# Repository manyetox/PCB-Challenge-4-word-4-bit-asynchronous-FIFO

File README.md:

# PCB Challenge 2026 – Submission

**Files**
- `pcb_challenge_final.kicad_pcb` / `.kicad_pro` / `.kicad_sch`: the KiCad 10 project. The schematic is unchanged from the challenge repo.
- `answer.md`: the logic deduction. The board is a 4-word × 4-bit asynchronous (dual-clock) FIFO.

## Board summary

| Item | Value |
|------|-------|
| Outline | Rectangle, **44 × 44 mm = 1936 mm²**. The Edge.Cuts line is 0.01 mm wide. |
| Content | 164 footprints, 411 vias (all 0.6/0.3 mm through vias) |
| Stack-up | 4 layers, 1.6 mm: F.Cu / 0.1 mm prepreg / In1.Cu / 1.24 mm core / In2.Cu / 0.1 mm prepreg / B.Cu |
| F.Cu | Components, signals, GND pour |
| In1.Cu | Solid GND plane. This is the reference for the USB D+/D− pair, which is routed on F.Cu with no vias, ≈28 mm long and length-matched. |
| In2.Cu | Signals plus a +3.3 V pour |
| B.Cu | Components, signals, GND pour |
| Rules (board setup + Default netclass) | 0.15 mm min track, 0.12 mm clearance, 0.6/0.3 mm vias (0.15 mm annular ring), 0.3 mm copper-to-edge, 0.25 mm hole-to-hole, 0.15 mm copper-to-hole |
| Power traces | +3.3 V / +5 V / GND are widened to 0.2–0.5 mm wherever clearance allows |
| Flip-flop pads (XSON6) | Only 0.15 mm tracks |

**Placement**
- Components are on both sides.
- The ESP32-S3 module sits in the top-right corner. Its antenna and antenna keep-out hang over the top board edge, which the rules allow.
- USB-C is on the bottom edge, below the module.

## Rule compliance

These were checked with KiCad's DRC and an independent script:
- **No unconnected items, no clearance, short or crossing errors.**
- **No vias inside any IC courtyard**, top or bottom. This includes the flip-flops' courtyard, which the library footprint places on the opposite side.
- **No foreign tracks inside an IC courtyard on the IC's own layer.** Each IC pin escapes straight out of its own pad.
- **The ESP32 module's ground pads** are a separate schematic net (`Net-(U25-GND-Pad2)`). They are joined by a small copper zone under the module, inside the pad ring.
- **Footprints are unmodified.**
  - SW2 and U25 were reloaded from the stock KiCad library, because the original PCB still had an old SW2 footprint.
  - Reference designators were moved to the Fab layers to keep the silkscreen clear. KiCad's library-mismatch check ignores this.

## Remaining DRC items (none come from the layout)
- `malformed_courtyard` on the XSON6 flip-flops (U1, U4…): this is the known flip-flop footprint issue mentioned in the challenge README.
- `lib_footprint_issues`: the custom `reg` / `adder` / `3v3_ldo` libraries are not installed on this machine.
- Schematic parity: symbol pins with no footprint pad. These are the NC pin 7 on the 6-pad muxes, J3's unused pins, and SW2 pins 3/4. They come from the provided schematic/footprints.
- Two `silk_edge_clearance` warnings. They are the ESP32's own silkscreen running past the board edge, where the antenna overhangs.

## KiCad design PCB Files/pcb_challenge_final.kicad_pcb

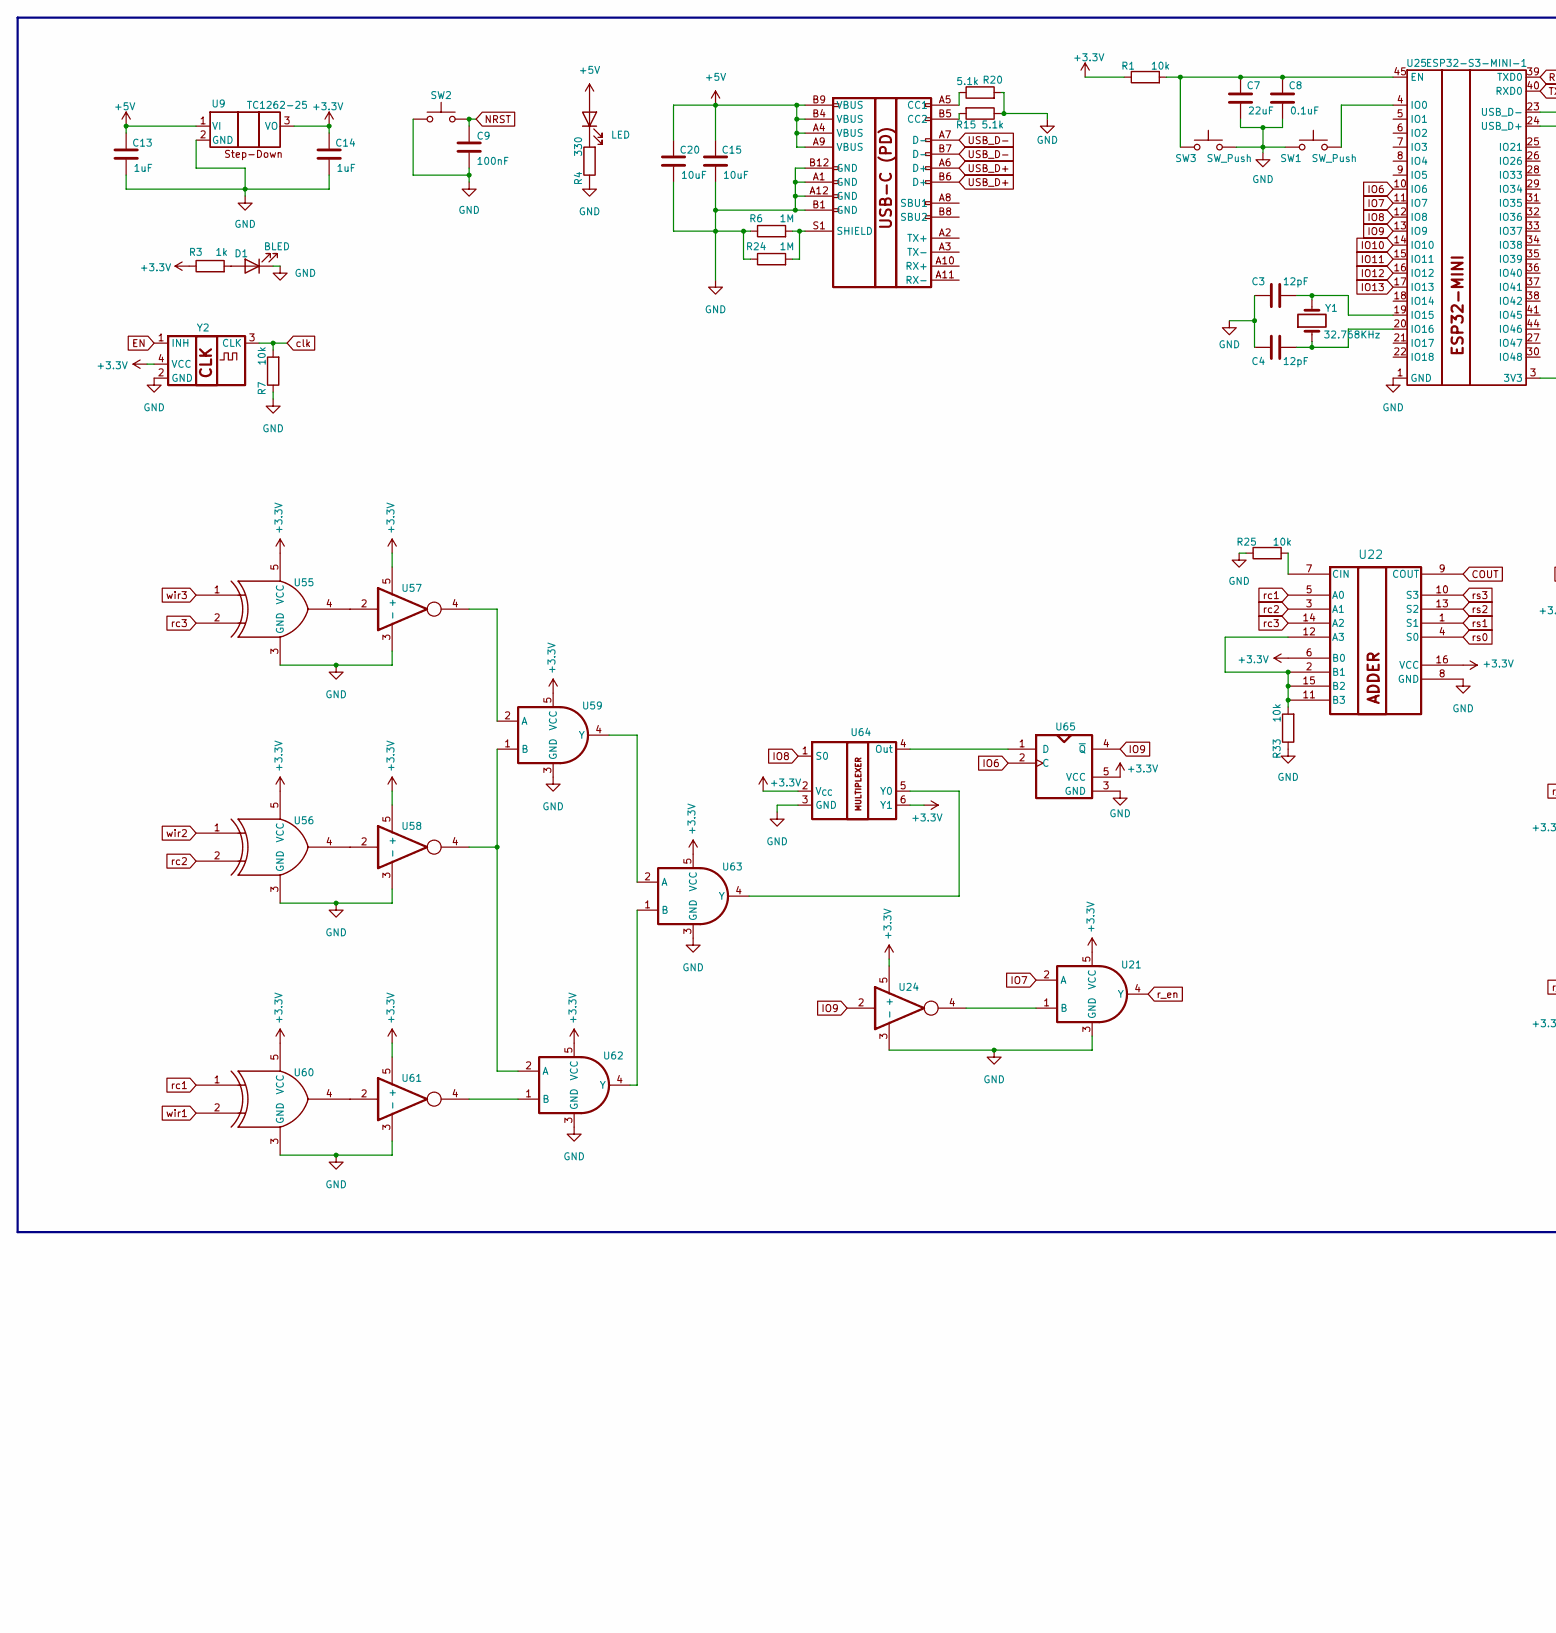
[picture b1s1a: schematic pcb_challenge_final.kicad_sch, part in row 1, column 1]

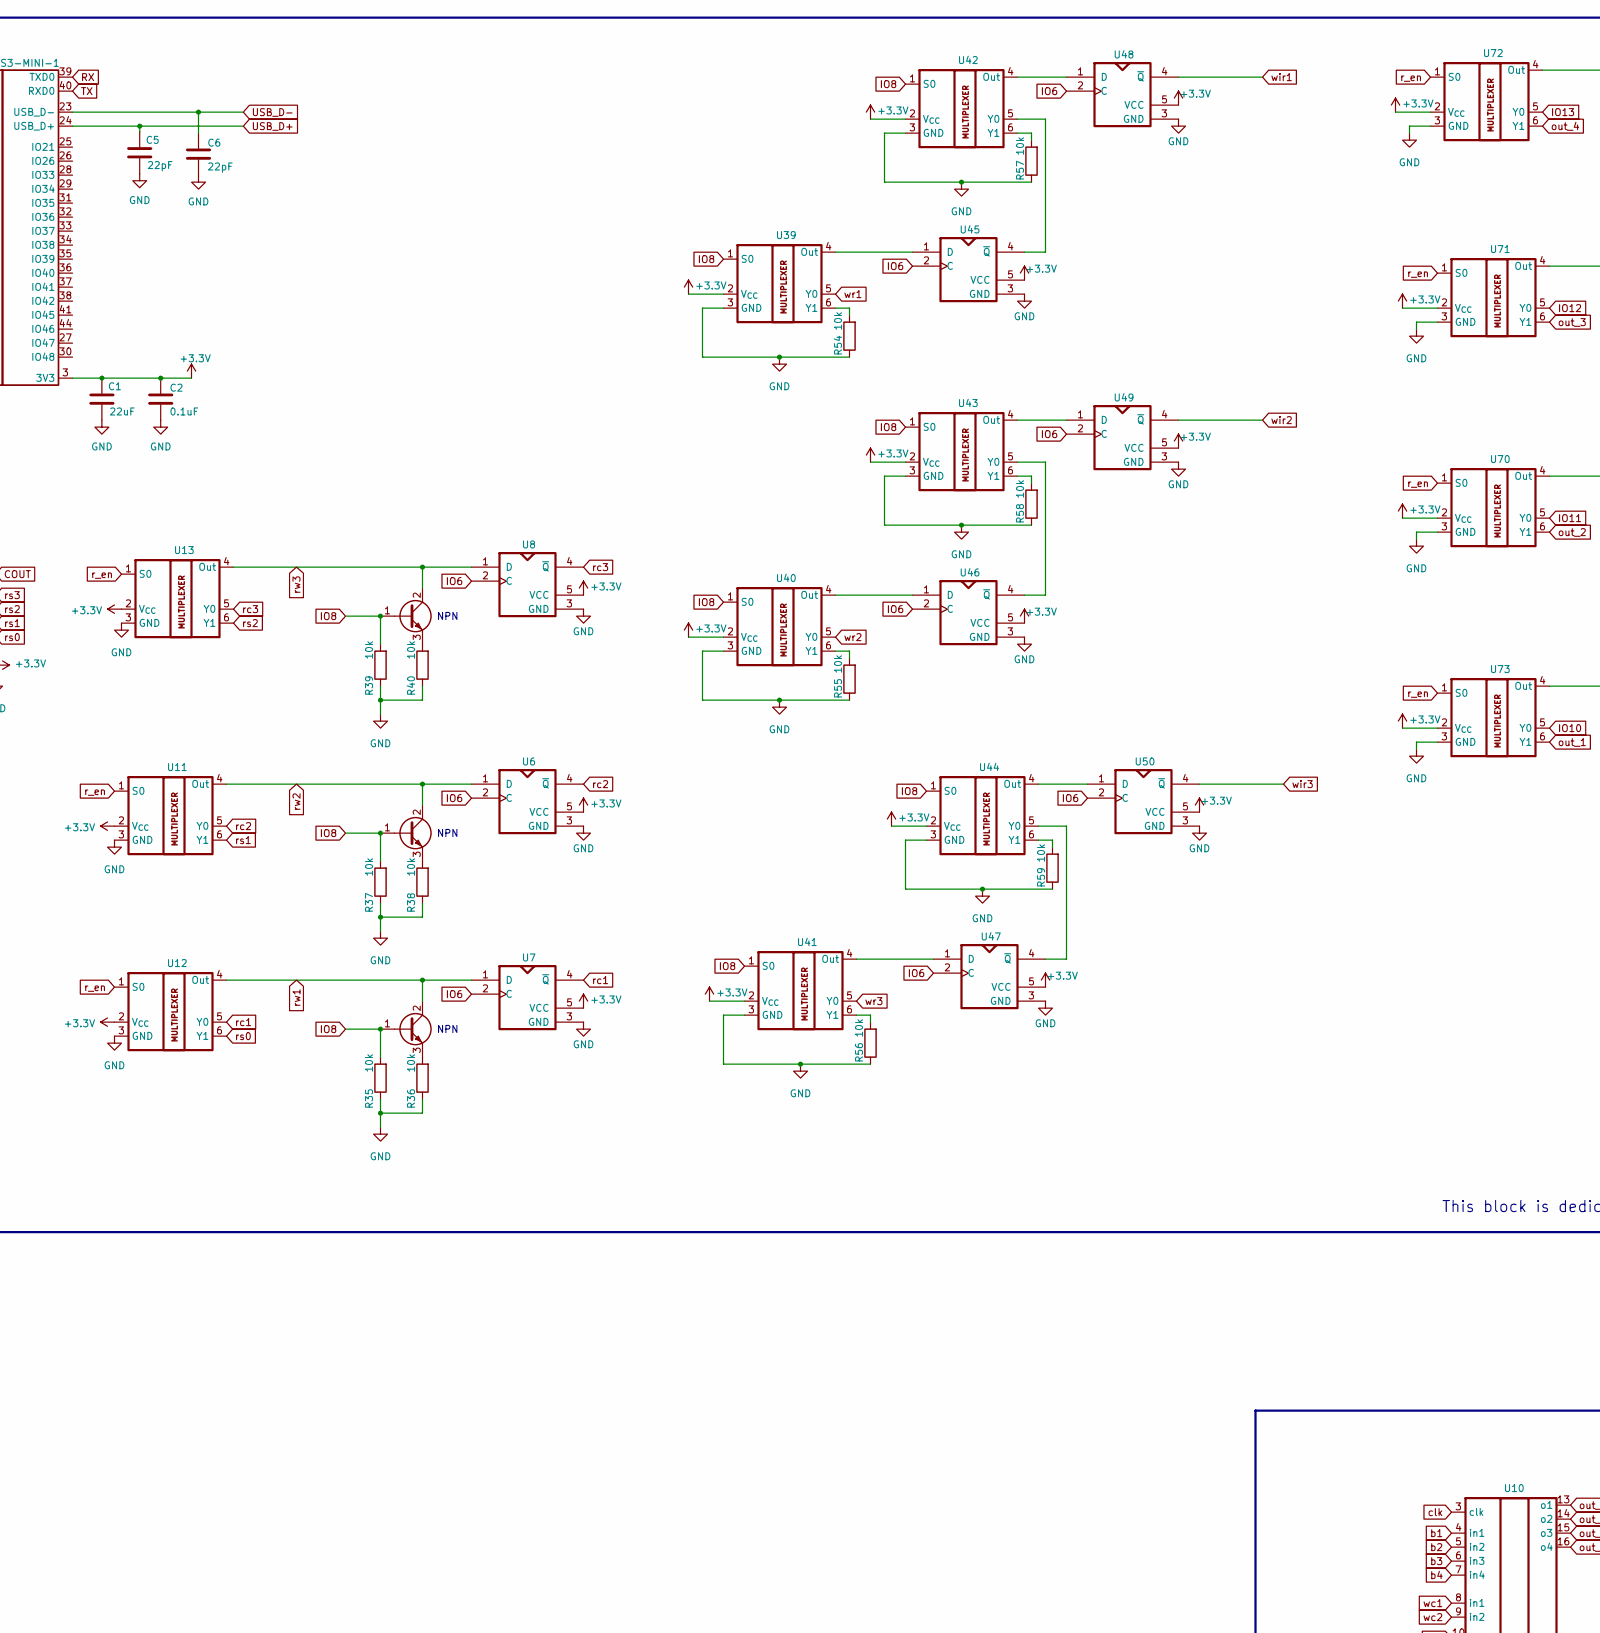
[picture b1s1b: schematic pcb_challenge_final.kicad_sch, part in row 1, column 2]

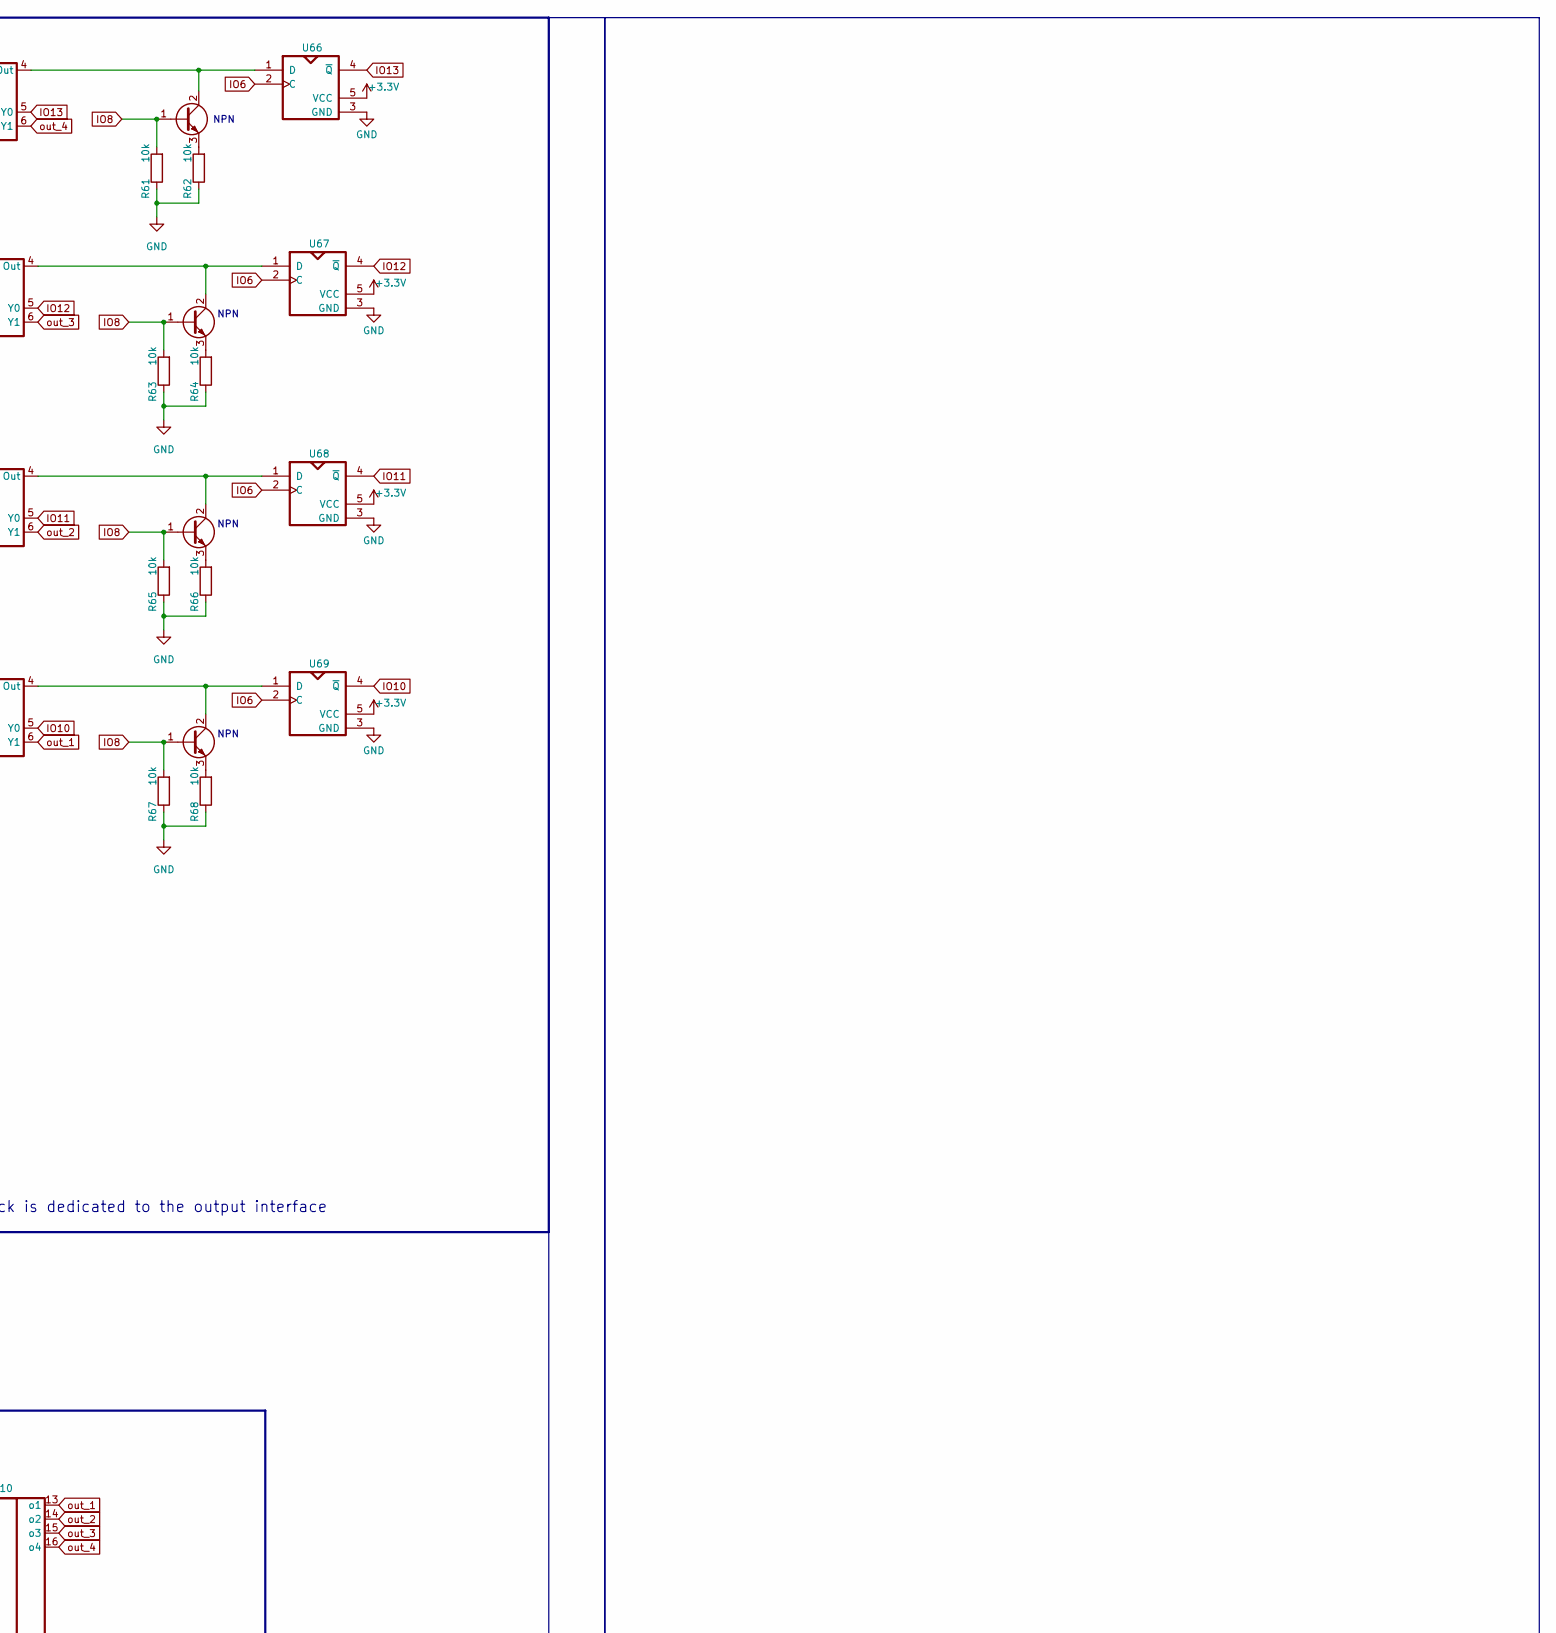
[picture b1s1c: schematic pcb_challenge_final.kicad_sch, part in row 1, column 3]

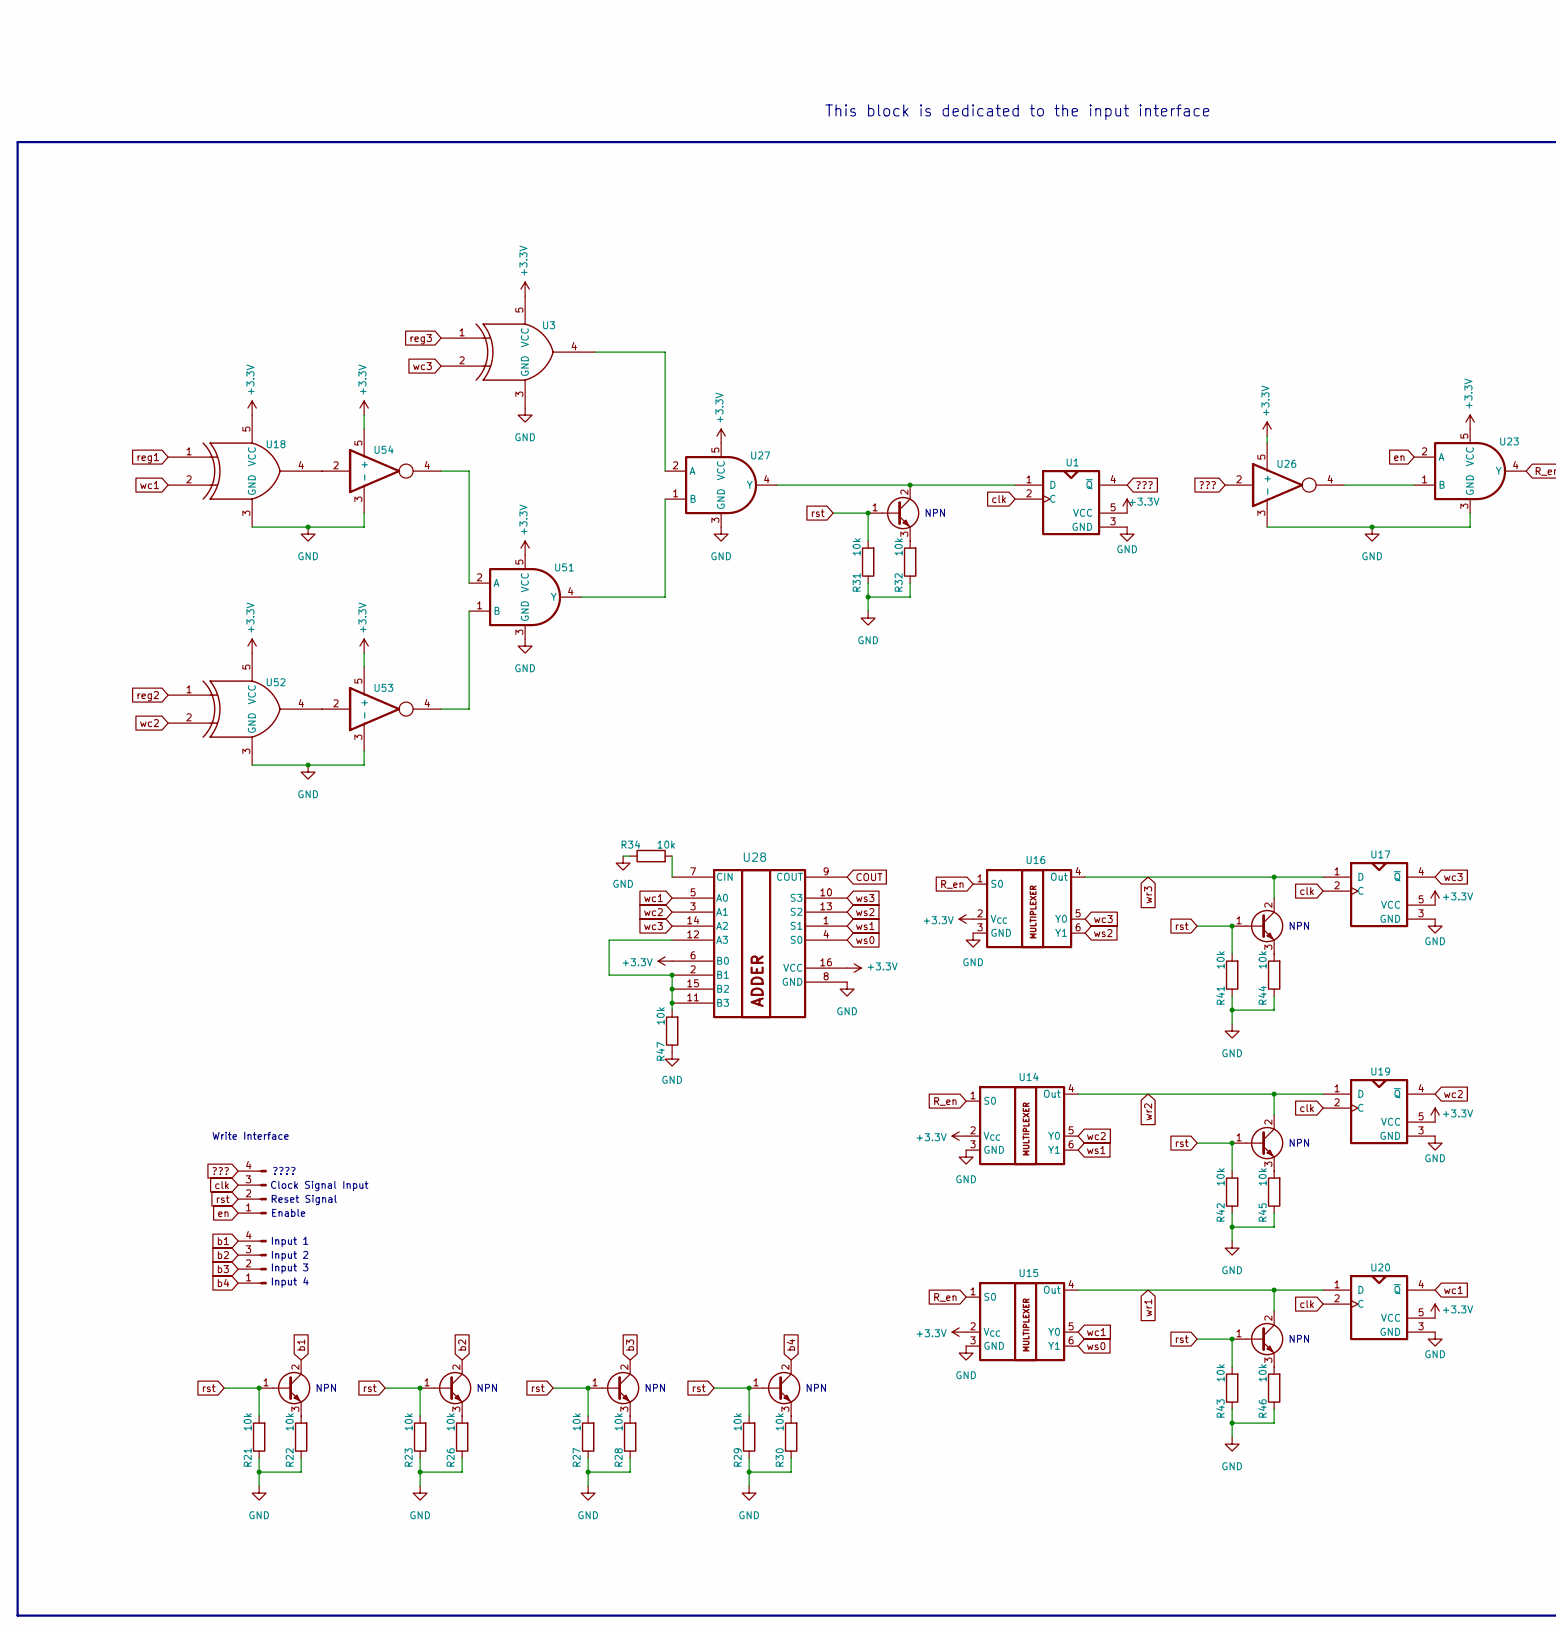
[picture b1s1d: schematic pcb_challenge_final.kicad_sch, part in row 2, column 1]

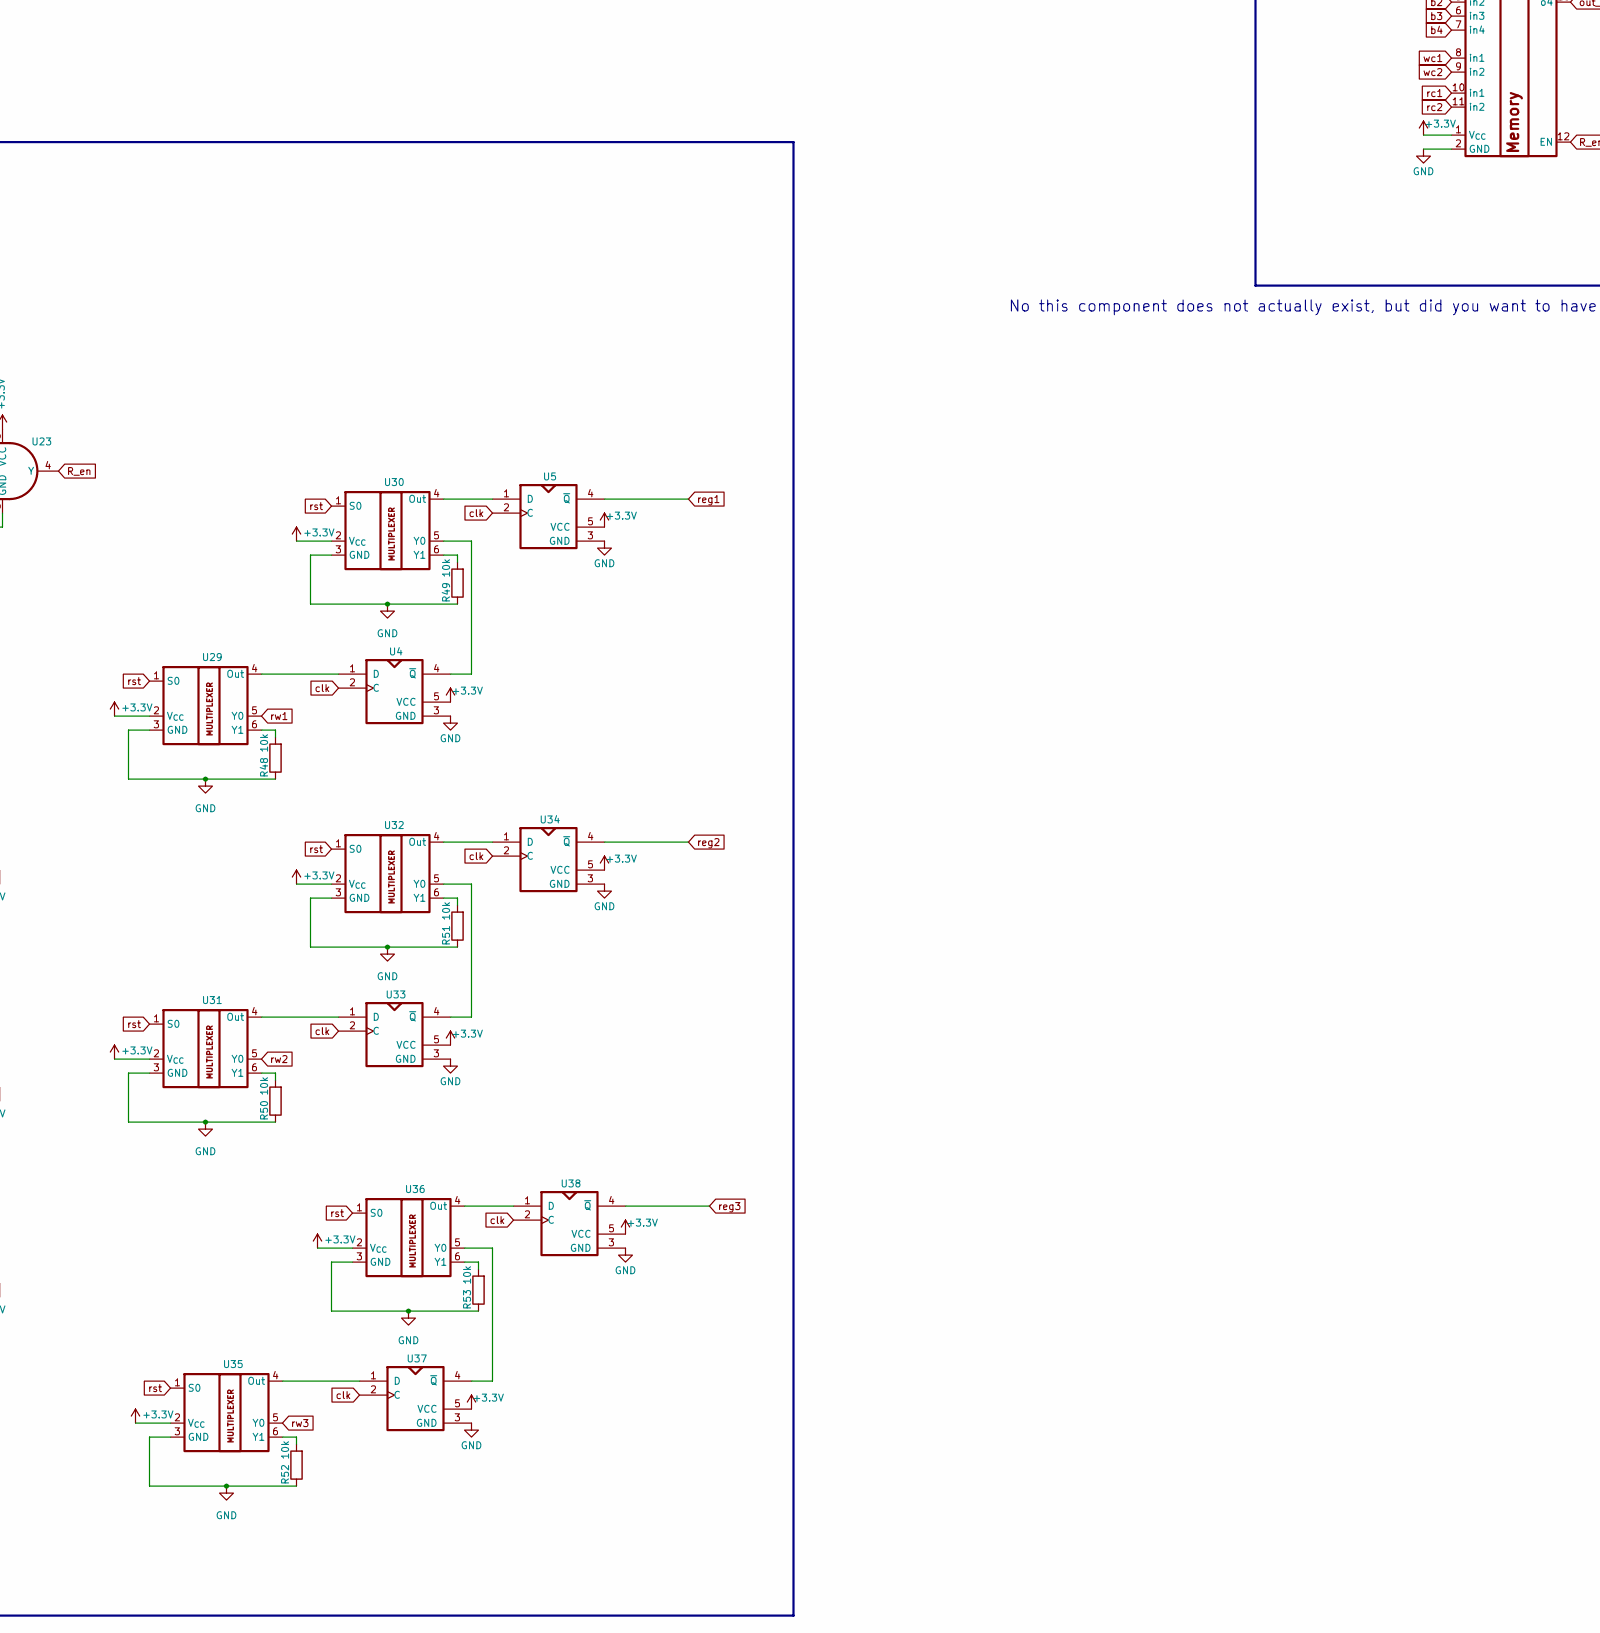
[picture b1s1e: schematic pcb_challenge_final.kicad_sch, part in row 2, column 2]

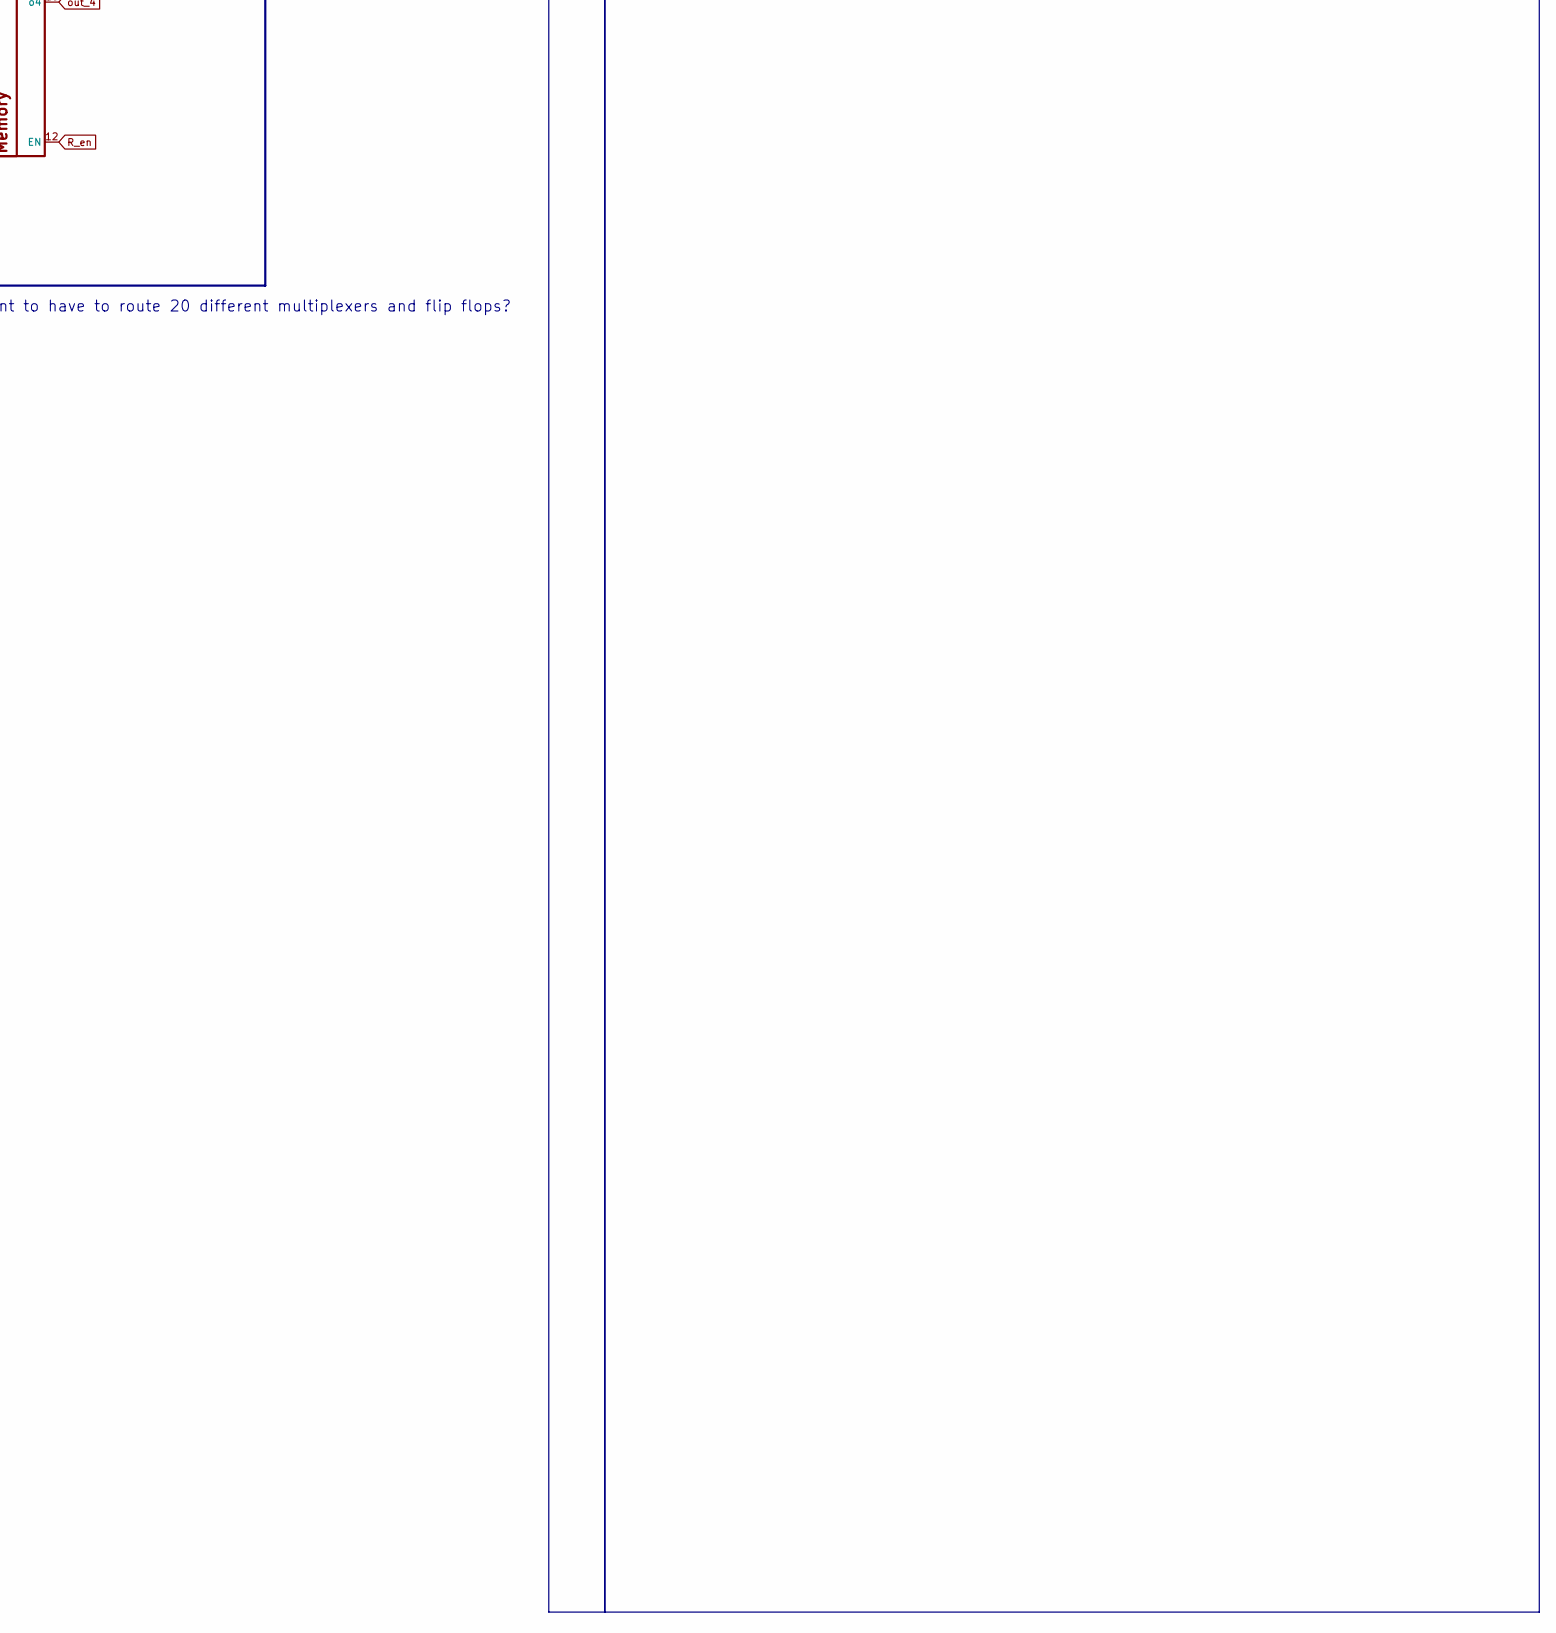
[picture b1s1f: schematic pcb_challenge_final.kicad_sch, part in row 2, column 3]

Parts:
C1, C7: 22uF; C_0201_0603Metric
C2, C8: 0.1uF; C_0201_0603Metric
C3, C4: 12pF; C_0201_0603Metric
C5, C6: 22pF; C_0201_0603Metric
C9: 100nF; C_0402_1005Metric
C13, C14: 1uF; C_0603_1608Metric
C15, C20: 10uF; C_0603_1608Metric
D1: BLED; LED_0603_1608Metric
GREEN_LED1: LED; LED_0603_1608Metric
J3: USB_C_Receptacle_HCTL_HC-TYPE-C-16P-01A
J4, J5: Conn_01x04_Pin; PinHeader_1x04_P2.54mm_Vertical
Q15, Q16, Q17, Q18, Q19, Q20, Q21, Q22, Q23, Q24, Q25, Q26, Q27, Q28, Q29: Q_Dual_NPN_PNP_B1E2B2C2E1C1; SOT-1123
R1: 10k; C_0402_1005Metric
R3: 1k; C_0603_1608Metric
R4: 330; C_0603_1608Metric
R6, R24: 1M; C_0603_1608Metric
R7, R21, R22, R23, R25, R26, R27, R28, R29, R30, R31, R32, R33, R34, R35, R36, R37, R38, R39, R40, R41, R42, R43, R44, R45, R46, R47, R48, R49, R50, R51, R52, R53, R54, R55, R56, R57, R58, R59, R61, R62, R63, R64, R65, R66, R67, R68: 10k; C_0603_1608Metric
R15, R20: 5.1k; R_0603_1608Metric_Pad0.98x0.95mm_HandSolder
SW1, SW3: SW_Push; SW_DIP_SPSTx01_Slide_6.7x4.1mm_W8.61mm_P2.54mm_LowProfile
SW2: SW_MEC_5G; SW_SPST_CK_RS282G05A3
U1, U4, U5, U6, U7, U8, U17, U19, U20, U33, U34, U37, U38, U45, U46, U47, U48, U49, U50, U65, U66, U67, U68, U69: 74AUP1G80; XSON6_SOT1115_NEX
U3, U18, U52, U55, U56, U60: 74AHC1G86; SC-74A-5_1.55x2.9mm_P0.95mm
U9: TC1262-25; SOT-223_3MC_MCH
U10: NMUX1308BQ; SO-16_3.9x9.9mm_P1.27mm
U11, U12, U13, U14, U15, U16, U29, U30, U31, U32, U35, U36, U39, U40, U41, U42, U43, U44, U64, U70, U71, U72, U73: NMUX1308BQ; SOT-363_SC-70-6
U21, U23, U27, U51, U59, U62, U63: 74LV1T08GV; SC-74A-5_1.55x2.9mm_P0.95mm
U22, U28: CD74HC283M96; D16
U24, U26, U53, U54, U57, U58, U61: 74LVC1GU04DRL; SOT-553
U25: ESP32-S3-MINI-1; ESP32-S2-MINI-1
Y1: 32.768KHz; Crystal_SMD_Abracon_ABM7-2Pin_6.0x3.5mm
Y2: KC2520Z; Oscillator_SMD_Kyocera_KC2520Z-4Pin_2.5x2.0mm

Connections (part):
+3.3V: C1.1, C2.1, C14.1, R1.1, R3.1, U1.5 (VCC), U3.5 (VCC), U4.5 (VCC), U5.5 (VCC), U6.5 (VCC), U7.5 (VCC), U8.5 (VCC), U9.3 (VO), U10.1 (V_{CC}), U11.2 (V_{CC}), U12.2 (V_{CC}), U13.2 (V_{CC}), U14.2 (V_{CC}), U15.2 (V_{CC}), U16.2 (V_{CC}), U17.5 (VCC), U18.5 (VCC), U19.5 (VCC), U20.5 (VCC), U21.5 (VCC), U22.6 (B0), U22.16 (VCC), U23.5 (VCC), U24.5 (+), U25.3 (3V3), U26.5 (+), U27.5 (VCC), U28.6 (B0), U28.16 (VCC), U29.2 (V_{CC}), U30.2 (V_{CC}), U31.2 (V_{CC}), U32.2 (V_{CC}), U33.5 (VCC), U34.5 (VCC), U35.2 (V_{CC}), U36.2 (V_{CC}), U37.5 (VCC), U38.5 (VCC), U39.2 (V_{CC}), U40.2 (V_{CC}), U41.2 (V_{CC}), U42.2 (V_{CC}), U43.2 (V_{CC}), U44.2 (V_{CC}), U45.5 (VCC), U46.5 (VCC), U47.5 (VCC), U48.5 (VCC), U49.5 (VCC), U50.5 (VCC), U51.5 (VCC), U52.5 (VCC), U53.5 (+), U54.5 (+), U55.5 (VCC), U56.5 (VCC), U57.5 (+), U58.5 (+), U59.5 (VCC), U60.5 (VCC), U61.5 (+), U62.5 (VCC), U63.5 (VCC), U64.2 (V_{CC}), U64.6 (Y1), U65.5 (VCC), U66.5 (VCC), U67.5 (VCC), U68.5 (VCC), U69.5 (VCC), U70.2 (V_{CC}), U71.2 (V_{CC}), U72.2 (V_{CC}), U73.2 (V_{CC})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
+5V: C13.1, C15.1, C20.1, GREEN_LED1.2 (A), J3.A4 (VBUS), J3.A9 (VBUS), J3.B4 (VBUS), J3.B9 (VBUS), U9.1 (VI)
???: J5.4, U1.4 (~Q), U26.2
COUT: U22.9 (COUT), U28.9 (COUT)
EN: Y2.1 (INH)
GND: C1.2, C2.2, C3.1, C4.1, C5.2, C6.2, C7.2, C8.2, C9.2, C13.2, C14.2, C15.2, C20.2, D1.1 (K), J3.A1 (GND), J3.A12 (GND), J3.B1 (GND), J3.B12 (GND), R4.1, R6.1, R7.1, R15.1, R20.2, R21.1, R22.1, R23.1, R24.1, R25.1, R26.1, R27.1, R28.1, R29.1, R30.1, R31.1, R32.1, R33.1, R34.1, R35.1, R36.1, R37.1, R38.1, R39.1, R40.1, R41.1, R42.1, R43.1, R44.1, R45.1, R46.1, R47.1, R48.1, R49.1, R50.1, R51.1, R52.1, R53.1, R54.1, R55.1, R56.1, R57.1, R58.1, R59.1, R61.1, R62.1, R63.1, R64.1, R65.1, R66.1, R67.1, R68.1, SW1.1, SW2.1 (A), SW2.2 (A), SW3.2, U1.3 (GND), U3.3 (GND), U4.3 (GND), U5.3 (GND), U6.3 (GND), U7.3 (GND)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
IO6: U6.2 (C), U7.2 (C), U8.2 (C), U25.10 (IO6), U45.2 (C), U46.2 (C), U47.2 (C), U48.2 (C), U49.2 (C), U50.2 (C), U65.2 (C), U66.2 (C), U67.2 (C), U68.2 (C), U69.2 (C)
IO7: U21.2 (A), U25.11 (IO7)
IO8: Q18.1 (B1), Q19.1 (B1), Q20.1 (B1), Q24.1 (B1), Q25.1 (B1), Q26.1 (B1), Q27.1 (B1), R35.2, R37.2, R39.2, R61.2, R63.2, R65.2, R67.2, U25.12 (IO8), U39.1 (S0), U40.1 (S0), U41.1 (S0), U42.1 (S0), U43.1 (S0), U44.1 (S0), U64.1 (S0)
IO9: U24.2, U25.13 (IO9), U65.4 (~Q)
IO10: U25.14 (IO10), U69.4 (~Q), U73.5 (Y0)
IO11: U25.15 (IO11), U68.4 (~Q), U70.5 (Y0)
IO12: U25.16 (IO12), U67.4 (~Q), U71.5 (Y0)
IO13: U25.17 (IO13), U66.4 (~Q), U72.5 (Y0)
NRST: C9.1, SW2.3 (B), SW2.4 (B)
unnamed: D1.2 (A), R3.2
unnamed: GREEN_LED1.1 (K), R4.2
unnamed: J3.A5 (CC1), R20.1
unnamed: J3.B5 (CC2), R15.2
unnamed: J3.S1 (SHIELD), R6.2, R24.2
unnamed: Q15.3 (E1), R30.2
unnamed: Q16.2 (C1), U1.1 (D), U27.4 (Y)
unnamed: Q16.3 (E1), R32.2
unnamed: Q17.3 (E1), R28.2
unnamed: Q18.3 (E1), R40.2
unnamed: Q19.3 (E1), R38.2
unnamed: Q20.3 (E1), R36.2
unnamed: Q21.3 (E1), R44.2
unnamed: Q22.3 (E1), R45.2
unnamed: Q23.3 (E1), R46.2
unnamed: Q24.2 (C1), U66.1 (D), U72.4 (Out)
unnamed: Q24.3 (E1), R62.2
unnamed: Q25.2 (C1), U67.1 (D), U71.4 (Out)
unnamed: Q25.3 (E1), R64.2
unnamed: Q26.2 (C1), U68.1 (D), U70.4 (Out)
unnamed: Q26.3 (E1), R66.2
unnamed: Q27.2 (C1), U69.1 (D), U73.4 (Out)
unnamed: Q27.3 (E1), R68.2
unnamed: Q28.3 (E1), R26.2
unnamed: Q29.3 (E1), R22.2
unnamed: U18.4, U54.2
unnamed: U21.1 (B), U24.4
unnamed: R33.2, U22.2 (B1), U22.11 (B3), U22.12 (A3), U22.15 (B2)
unnamed: R25.2, U22.7 (CIN)
unnamed: U23.1 (B), U26.4
unnamed: C7.1, C8.1, R1.2, SW3.1, U25.45 (EN)
unnamed: U25.2 (GND), U25.42 (GND), U25.43 (GND), U25.46 (GND), U25.47 (GND), U25.48 (GND), U25.49 (GND), U25.50 (GND), U25.51 (GND), U25.52 (GND), U25.53 (GND), U25.54 (GND), U25.55 (GND), U25.56 (GND), U25.57 (GND), U25.58 (GND), U25.59 (GND), U25.60 (GND), U25.61 (GND), U25.62 (GND), U25.63 (GND), U25.64 (GND), U25.65 (GND)
unnamed: SW1.2, U25.4 (IO0)
unnamed: C3.2, U25.19 (IO15), Y1.2
unnamed: C4.2, U25.20 (IO16), Y1.1
unnamed: U3.4, U27.2 (A)
unnamed: U27.1 (B), U51.4 (Y)
unnamed: R47.2, U28.2 (B1), U28.11 (B3), U28.12 (A3), U28.15 (B2)
unnamed: R34.2, U28.7 (CIN)
unnamed: U4.1 (D), U29.4 (Out)
unnamed: R48.2, U29.6 (Y1)
unnamed: U5.1 (D), U30.4 (Out)
unnamed: U4.4 (~Q), U30.5 (Y0)
unnamed: R49.2, U30.6 (Y1)
unnamed: U31.4 (Out), U33.1 (D)
unnamed: R50.2, U31.6 (Y1)
unnamed: U32.4 (Out), U34.1 (D)
unnamed: U32.5 (Y0), U33.4 (~Q)
unnamed: R51.2, U32.6 (Y1)
unnamed: U35.4 (Out), U37.1 (D)
unnamed: R52.2, U35.6 (Y1)
unnamed: U36.4 (Out), U38.1 (D)
unnamed: U36.5 (Y0), U37.4 (~Q)
unnamed: R53.2, U36.6 (Y1)
unnamed: U39.4 (Out), U45.1 (D)
unnamed: R54.2, U39.6 (Y1)
unnamed: U40.4 (Out), U46.1 (D)
unnamed: R55.2, U40.6 (Y1)
unnamed: U41.4 (Out), U47.1 (D)
unnamed: R56.2, U41.6 (Y1)
unnamed: U42.4 (Out), U48.1 (D)
unnamed: U42.5 (Y0), U45.4 (~Q)
unnamed: R57.2, U42.6 (Y1)
unnamed: U43.4 (Out), U49.1 (D)
unnamed: U43.5 (Y0), U46.4 (~Q)
unnamed: R58.2, U43.6 (Y1)
unnamed: U44.4 (Out), U50.1 (D)
unnamed: U44.5 (Y0), U47.4 (~Q)
unnamed: R59.2, U44.6 (Y1)
unnamed: U51.2 (A), U54.4
unnamed: U51.1 (B), U53.4
unnamed: U52.4, U53.2
unnamed: U55.4, U57.2
unnamed: U56.4, U58.2
unnamed: U57.4, U59.2 (A)
unnamed: U58.4, U59.1 (B), U62.2 (A)
unnamed: U59.4 (Y), U63.2 (A)
unnamed: U60.4, U61.2
unnamed: U61.4, U62.1 (B)
unnamed: U62.4 (Y), U63.1 (B)
unnamed: U63.4 (Y), U64.5 (Y0)
unnamed: U64.4 (Out), U65.1 (D)
RX: U25.39 (TXD0)
R_en: U10.12 (EN), U14.1 (S0), U15.1 (S0), U16.1 (S0), U23.4 (Y)
TX: U25.40 (RXD0)
USB_D+: C5.1, J3.A6 (D+), J3.B6 (D+), U25.24 (USB_D+)
USB_D-: C6.1, J3.A7 (D-), J3.B7 (D-), U25.23 (USB_D-)
b1: J4.4, Q29.2 (C1), U10.4 (in1)
b2: J4.3, Q28.2 (C1), U10.5 (in2)
b3: J4.2, Q17.2 (C1), U10.6 (in3)
b4: J4.1, Q15.2 (C1), U10.7 (in4)
clk: J5.3, R7.2, U1.2 (C), U4.2 (C), U5.2 (C), U10.3 (clk), U17.2 (C), U19.2 (C), U20.2 (C), U33.2 (C), U34.2 (C), U37.2 (C), U38.2 (C), Y2.3 (CLK)
en: J5.1, U23.2 (A)
out_1: U10.13 (o1), U73.6 (Y1)
out_2: U10.14 (o2), U70.6 (Y1)
out_3: U10.15 (o3), U71.6 (Y1)
out_4: U10.16 (o4), U72.6 (Y1)
r_en: U11.1 (S0), U12.1 (S0), U13.1 (S0), U21.4 (Y), U70.1 (S0), U71.1 (S0), U72.1 (S0), U73.1 (S0)
rc1: U7.4 (~Q), U10.10 (in1), U12.5 (Y0), U22.5 (A0), U60.1
rc2: U6.4 (~Q), U10.11 (in2), U11.5 (Y0), U22.3 (A1), U56.2
rc3: U8.4 (~Q), U13.5 (Y0), U22.14 (A2), U55.2
reg1: U5.4 (~Q), U18.1
reg2: U34.4 (~Q), U52.1
reg3: U3.1, U38.4 (~Q)
rs0: U12.6 (Y1), U22.4 (S0)
rs1: U11.6 (Y1), U22.1 (S1)
rs2: U13.6 (Y1), U22.13 (S2)
rs3: U22.10 (S3)
rst: J5.2, Q15.1 (B1), Q16.1 (B1), Q17.1 (B1), Q21.1 (B1), Q22.1 (B1), Q23.1 (B1), Q28.1 (B1), Q29.1 (B1), R21.2, R23.2, R27.2, R29.2, R31.2, R41.2, R42.2, R43.2, U29.1 (S0), U30.1 (S0), U31.1 (S0), U32.1 (S0), U35.1 (S0), U36.1 (S0)
rw1: Q20.2 (C1), U7.1 (D), U12.4 (Out), U29.5 (Y0)
rw2: Q19.2 (C1), U6.1 (D), U11.4 (Out), U31.5 (Y0)
rw3: Q18.2 (C1), U8.1 (D), U13.4 (Out), U35.5 (Y0)
wc1: U10.8 (in1), U15.5 (Y0), U18.2, U20.4 (~Q), U28.5 (A0)
wc2: U10.9 (in2), U14.5 (Y0), U19.4 (~Q), U28.3 (A1), U52.2
wc3: U3.2, U16.5 (Y0), U17.4 (~Q), U28.14 (A2)
wir1: U48.4 (~Q), U60.2
wir2: U49.4 (~Q), U56.1
wir3: U50.4 (~Q), U55.1
wr1: Q23.2 (C1), U15.4 (Out), U20.1 (D), U39.5 (Y0)
wr2: Q22.2 (C1), U14.4 (Out), U19.1 (D), U40.5 (Y0)
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
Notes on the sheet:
NPN
Reset Signal
This block is dedicated to the input interface
Clock Signal Input
Enable
Input 2
Input 3
No this component does not actually exist, but did you want to have to route 20 different multiplexers and flip flops?
????
Input 1
Input 4
Write Interface
This block is dedicated to the output interface

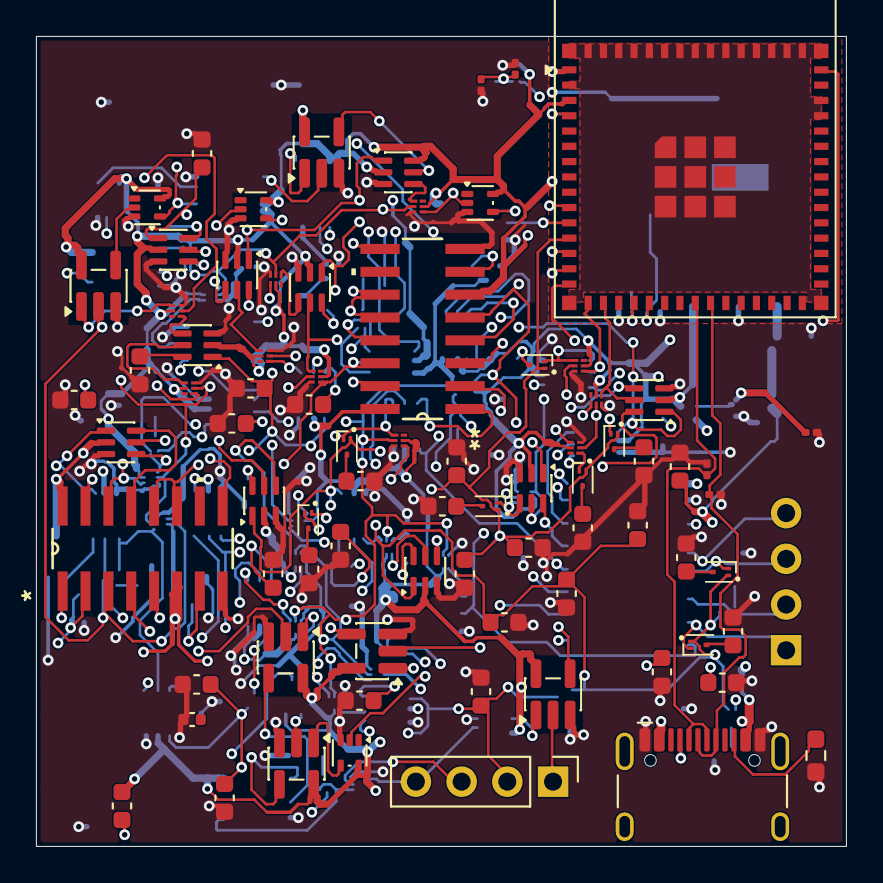
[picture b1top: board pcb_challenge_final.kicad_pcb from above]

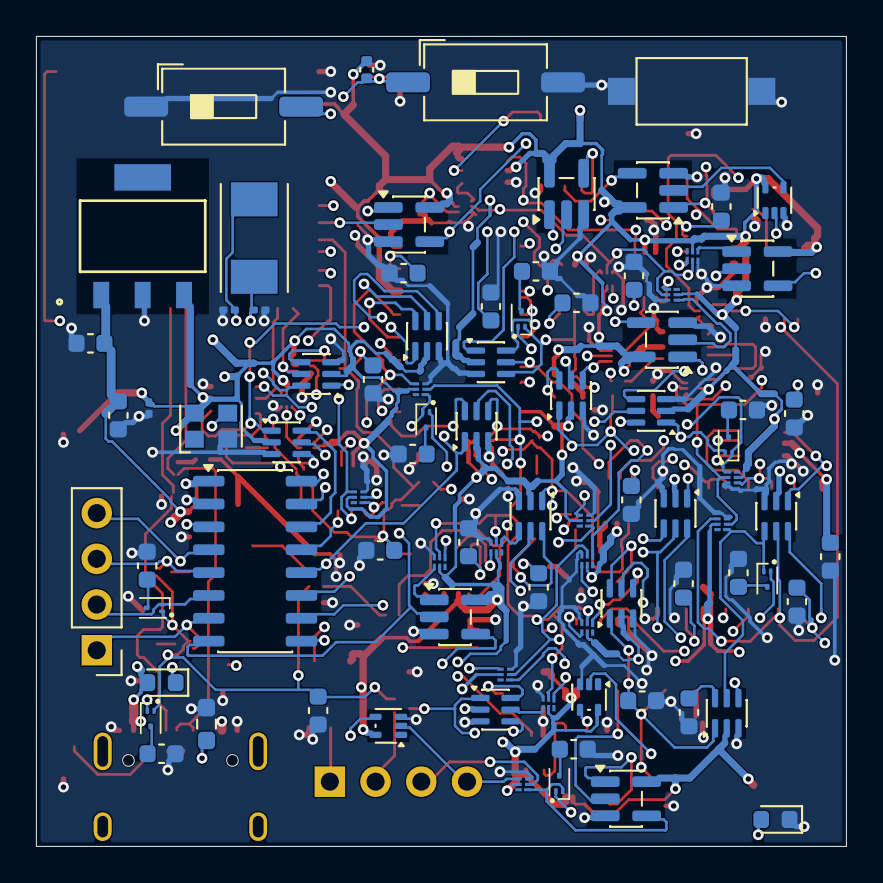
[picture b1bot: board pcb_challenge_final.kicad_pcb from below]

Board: 4 copper layers, 45.0 x 45.0 mm, 164 parts (85 on the bottom side), 134 nets.
